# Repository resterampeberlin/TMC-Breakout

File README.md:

# Purpose

# Credits

This open source code project is has been proudfully produced in Berlin (and other places around the globe) by

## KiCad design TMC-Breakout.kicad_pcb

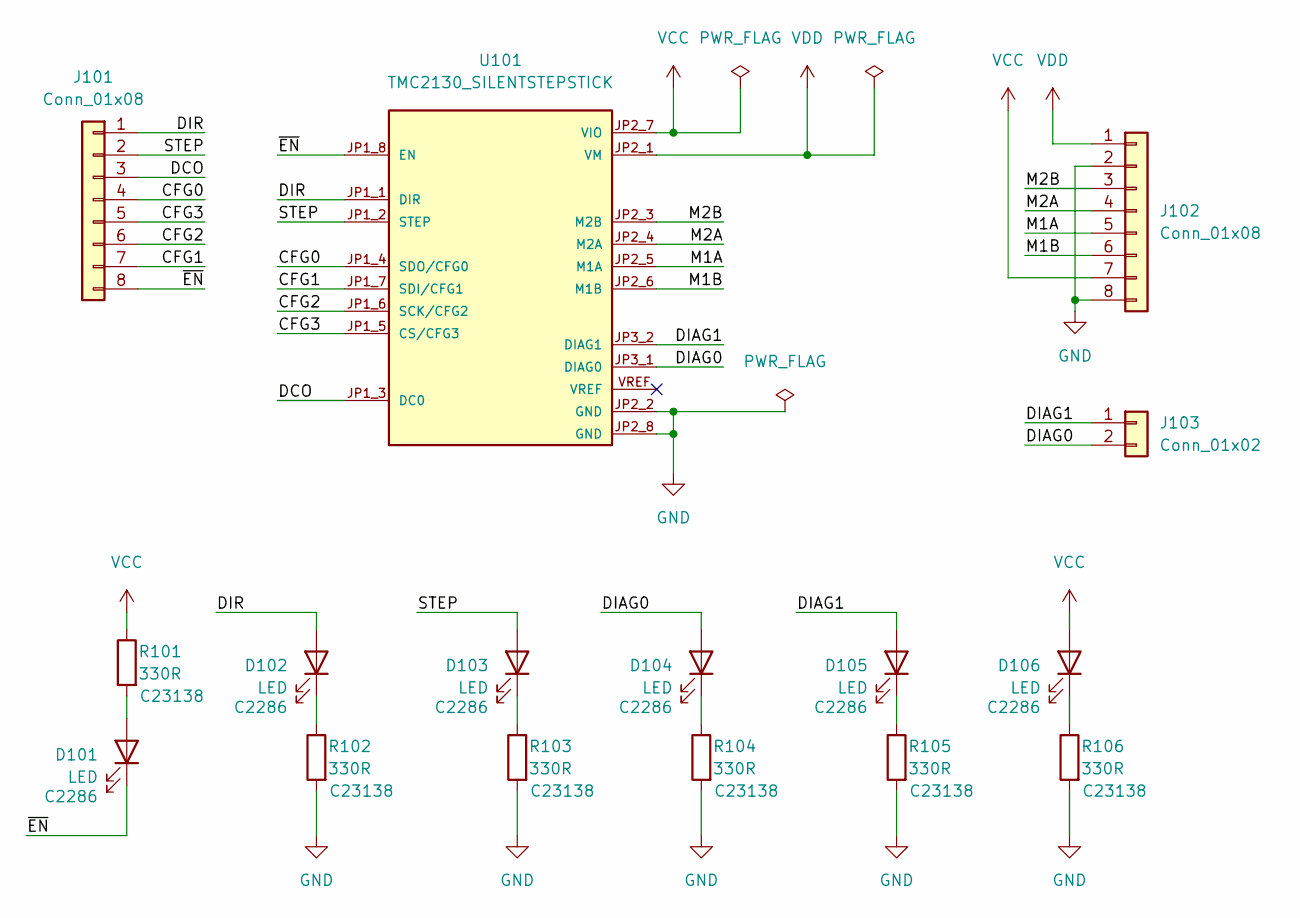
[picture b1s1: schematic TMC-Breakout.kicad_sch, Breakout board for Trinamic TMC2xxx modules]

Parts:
D101, D102, D103, D104, D105, D106: LED; LED_0603_1608Metric_Pad1.05x0.95mm_HandSolder; LCSC C2286
J101, J102: Conn_01x08; PinHeader_1x08_P2.54mm_Vertical
J103: Conn_01x02; PinHeader_1x02_P2.54mm_Vertical
R101, R102, R103, R104, R105, R106: 330R; R_0603_1608Metric_Pad0.98x0.95mm_HandSolder; LCSC C23138
U101: TMC2130_SILENTSTEPSTICK; MODULE_TMC2130_SILENTSTEPSTICK

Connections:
/CFG0: J101.4, U101.JP1_4 (SDO/CFG0)
/CFG1: J101.7, U101.JP1_7 (SDI/CFG1)
/CFG2: J101.6, U101.JP1_6 (SCK/CFG2)
/CFG3: J101.5, U101.JP1_5 (CS/CFG3)
/DCO: J101.3, U101.JP1_3 (DC0)
/DIAG0: D104.2 (A), J103.2, U101.JP3_1 (DIAG0)
/DIAG1: D105.2 (A), J103.1, U101.JP3_2 (DIAG1)
/DIR: D102.2 (A), J101.1, U101.JP1_1 (DIR)
/M1A: J102.5, U101.JP2_5 (M1A)
/M1B: J102.6, U101.JP2_6 (M1B)
/M2A: J102.4, U101.JP2_4 (M2A)
/M2B: J102.3, U101.JP2_3 (M2B)
/STEP: D103.2 (A), J101.2, U101.JP1_2 (STEP)
/~EN: D101.1 (K), J101.8, U101.JP1_8 (EN)
GND: J102.2, J102.8, R102.2, R103.2, R104.2, R105.2, R106.2, U101.JP2_2 (GND), U101.JP2_8 (GND)
unnamed: D101.2 (A), R101.2
unnamed: D102.1 (K), R102.1
unnamed: D103.1 (K), R103.1
unnamed: D104.1 (K), R104.1
unnamed: D105.1 (K), R105.1
unnamed: D106.1 (K), R106.1
VCC: D106.2 (A), J102.7, R101.1, U101.JP2_7 (VIO)
VDD: J102.1, U101.JP2_1 (VM)

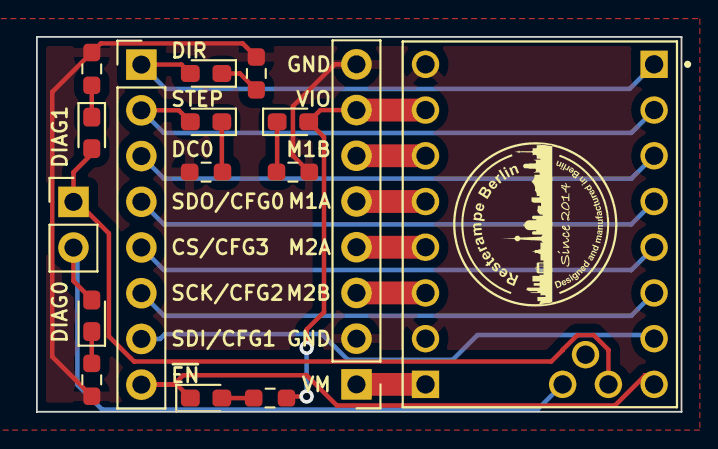
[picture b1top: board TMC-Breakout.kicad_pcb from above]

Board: 2 copper layers, 35.8 x 20.8 mm, 16 parts (0 on the bottom side), 23 nets.

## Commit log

2023-02-12 Production
2023-02-12 Project structure cleaned up

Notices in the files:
README.md:
License: CC BY-NC 4.0
TMC-Breakout.kicad_pcb:
https://creativecommons.org/licenses/by-nc/4.0
